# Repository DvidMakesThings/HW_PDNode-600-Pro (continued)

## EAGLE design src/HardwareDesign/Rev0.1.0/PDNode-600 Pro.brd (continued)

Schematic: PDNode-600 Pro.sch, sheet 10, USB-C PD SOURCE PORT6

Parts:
C136, C137: 1uF 10V; 0201
C138: 1uF 50V; C0603
C139: 4.7nF; C0402
C140: 4.7uF; C0402
C141, C142, C143: 10nF; 0201
C144, C145: 100nF; C0402
C146, C147, C148, C149: 10uF 50V; C0805
C150, C151, C152, C153: 22uF 50V; C0805
C154: 100nF; 0201
IC20: STUSB4710AQ1TR; QFN50P300X300X55-16N
IC32: TPS552882; RPM0026A-MFG
IC33: INA219BIDCNT; SOT23-8
L7: 4.7uH 744771004; WE-PD_1280
PORT6: 632722100213
R160: 200K; R0201
R161: 12.7K 0.1%; R0201
R162, R163: 4.64K 0.1%; R0201
R164: 8.87K 0.1%; R0201
R165: 30.9K 0.1%; R0201
R166: 100K; R0201
R167: DNI; R0201
R168, R169, R172: 10K; 0402
R170, R182: 10K; R0201
R171: 2.2K; R0201
R173, R179: 0.010R; 2512
R174: 6.19K; R0201
R175: 49.9K; R0201
R176, R178: 19.9K; R0201
R177: 150K; R0201
R180, R181: 1K; R0201
T31, T32, T33: DMP3013SFV; POWERDI3333-8_UX_DIO-L
T34, T35: BSZ065N06LS5ATMA1; POWERDI3333-8_UX_DIO-L

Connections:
+3V3: C154.1, IC33.4 (VCC), IC33.7 (A0), R166.1, R182.1; also elsewhere on the board
+24V_B: C146.1, C147.1, C148.1, C149.1, IC32.3 (VIN), T35.5 (D), T35.6 (D), T35.7 (D), T35.8 (D), T35.9 (D); also elsewhere on the board
AGND: C139.2, PORT6.S1 (SHIELD1), PORT6.S2 (SHIELD1), PORT6.S3 (SHIELD1), PORT6.S4 (SHIELD1), R172.2; also elsewhere on the board
CC1_PORT6: IC20.2 (CC1), PORT6.A5 (CC1)
CC2_PORT6: IC20.3 (CC2), PORT6.B5 (CC2)
EN_PORT6: IC32.4 (EN), R182.2; also elsewhere on the board
GND: C136.2, C137.2, C138.2, C139.1, C140.2, C141.2, C142.2, C143.2, C146.2, C147.2, C148.2, C149.2, C150.2, C151.2, C152.2, C153.2, C154.2, IC20.6 (GND), IC32.9 (PGND), IC32.10 (AGND), IC32.24 (PGND), IC33.3 (GND), IC33.8 (A1), PORT6.A12 (GND1), PORT6.B12 (GND2), R165.2, R167.2, R168.2, R172.1, R174.2, R175.2, R176.2, R177.2, T34.1 (S), T34.2 (S), T34.3 (S); also elsewhere on the board
IN1_PORT6: IC20.12 (VBUS_SENSE), IC33.1 (IN+), R173.1, T33.5 (D), T33.6 (D), T33.7 (D), T33.8 (D), T33.9 (D)
IN2_PORT6: IC33.2 (IN-), PORT6.A9 (VBUS1), PORT6.B9 (VBUS2), R173.2
unnamed: IC32.14 (FB), R160.2, R161.1
unnamed: IC20.11 (SEL_PDO5), R161.2, R162.1
unnamed: IC20.10 (SEL_PDO4), R162.2, R163.1
unnamed: IC20.7 (SEL_PDO3), R163.2, R164.1
unnamed: IC20.8 (SEL_PDO2), R164.2, R165.1
unnamed: C136.1, IC20.15 (VREG1V2)
unnamed: C137.1, IC20.16 (VREG2V7)
unnamed: IC20.9 (ADDR0), R166.2, R167.1
unnamed: R168.1, T31.5 (D), T31.6 (D), T31.7 (D), T31.8 (D), T31.9 (D)
unnamed: IC20.13 (VBUS_DISCH), R169.2, T31.4 (G)
unnamed: R170.1, T32.1 (S), T32.2 (S), T32.3 (S), T33.1 (S), T33.2 (S), T33.3 (S)
unnamed: R170.2, R171.1, T32.4 (G), T33.4 (G)
unnamed: IC20.14 (VBUS_EN_SRC), R171.2
unnamed: C143.1, R178.2
unnamed: IC32.8 (FSW), R175.1
unnamed: C141.1, IC32.7 (DITH_SYNC)
unnamed: IC32.15 (MODE), R174.1
unnamed: IC32.17 (ILIM), R176.1
unnamed: IC32.16 (CDC), R177.1
unnamed: C142.1, IC32.18 (COMP), R178.1
unnamed: C140.1, IC32.19 (VCC)
unnamed: C144.1, IC32.23 (SW1), L7.1, T34.5 (D), T34.6 (D), T34.7 (D), T34.8 (D), T34.9 (D), T35.1 (S), T35.2 (S), T35.3 (S)
unnamed: C145.1, IC32.21 (SW2), IC32.25 (SW2), L7.2
unnamed: C144.2, IC32.22 (BOOT1)
unnamed: C145.2, IC32.20 (BOOT2)
unnamed: R181.2, T35.4 (G)
unnamed: R180.2, T34.4 (G)
unnamed: IC32.1 (DR1L), R180.1
unnamed: IC32.2 (DR1H), R181.1
TCA2_I2C_SCL: IC20.4 (SCL); also elsewhere on the board
TCA2_I2C_SDA: IC20.5 (SDA); also elsewhere on the board
TCA5_I2C_SCL: IC33.5 (SCL); also elsewhere on the board
TCA5_I2C_SDA: IC33.6 (SDA); also elsewhere on the board
VOUT_PORT6: C150.1, C151.1, C152.1, C153.1, IC32.11 (VOUT), IC32.12 (ISP), IC32.26 (VOUT), R179.1
VSRC6: C138.1, IC20.1 (VDD), IC32.13 (ISN), R160.1, R169.1, R179.2, T31.1 (S), T31.2 (S), T31.3 (S), T32.5 (D), T32.6 (D), T32.7 (D), T32.8 (D), T32.9 (D)

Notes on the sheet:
PDNode-600 Pro
DvidMakesThings
David Sipos @2025
USB-C PD SOURCE PORT6
CURRENT MEASUREMENT
USB-C PD PORT6
v0.1.0
Output voltage: 5 V to 20 V Output current limit: 5 A
PD Ladder - TPS552882 (VREF = 1.20V, Rtop = 200kΩ) R25 = 12.7k → VOUT ≈ 20.10V R26 = 4.64k → VOUT ≈ 15.04V R27 = 4.64k → VOUT ≈ 12.12V R28 = 8.87k → VOUT ≈ 8.98V R29 = 30.9k → VOUT ≈ 5.09V Cumulative Rbottom = 61.75kΩ
Address: 0x40
Address: 0x28

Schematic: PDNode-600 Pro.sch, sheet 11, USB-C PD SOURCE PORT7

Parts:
C155, C156: 1uF 10V; 0201
C157: 1uF 50V; C0603
C158: 4.7nF; C0402
C159: 4.7uF; C0402
C160, C161, C162: 10nF; 0201
C163, C164: 100nF; C0402
C165, C166, C167, C168: 10uF 50V; C0805
C169, C170, C171, C172: 22uF 50V; C0805
C173: 100nF; 0201
IC23: STUSB4710AQ1TR; QFN50P300X300X55-16N
IC35: TPS552882; RPM0026A-MFG
IC36: INA219BIDCNT; SOT23-8
L8: 4.7uH 744771004; WE-PD_1280
PORT7: 632722100213
R183: 200K; R0201
R184: 12.7K 0.1%; R0201
R185, R186: 4.64K 0.1%; R0201
R187: 8.87K 0.1%; R0201
R188: 30.9K 0.1%; R0201
R189: DNI; R0201
R190: 100K; R0201
R191, R192, R195: 10K; 0402
R193, R218: 10K; R0201
R194: 2.2K; R0201
R196, R202: 0.010R; 2512
R197: 6.19K; R0201
R198: 49.9K; R0201
R199, R201: 19.9K; R0201
R200: 150K; R0201
R203, R204: 1K; R0201
T36, T37, T38: DMP3013SFV; POWERDI3333-8_UX_DIO-L
T39, T40: BSZ065N06LS5ATMA1; POWERDI3333-8_UX_DIO-L

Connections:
+3V3: C173.1, IC36.4 (VCC), IC36.8 (A1), R189.1, R218.1; also elsewhere on the board
+24V_B: C165.1, C166.1, C167.1, C168.1, IC35.3 (VIN), T40.5 (D), T40.6 (D), T40.7 (D), T40.8 (D), T40.9 (D); also elsewhere on the board
AGND: C158.2, PORT7.S1 (SHIELD1), PORT7.S2 (SHIELD1), PORT7.S3 (SHIELD1), PORT7.S4 (SHIELD1), R195.2; also elsewhere on the board
CC1_PORT7: IC23.2 (CC1), PORT7.A5 (CC1)
CC2_PORT7: IC23.3 (CC2), PORT7.B5 (CC2)
EN_PORT7: IC35.4 (EN), R218.2; also elsewhere on the board
GND: C155.2, C156.2, C157.2, C158.1, C159.2, C160.2, C161.2, C162.2, C165.2, C166.2, C167.2, C168.2, C169.2, C170.2, C171.2, C172.2, C173.2, IC23.6 (GND), IC35.9 (PGND), IC35.10 (AGND), IC35.24 (PGND), IC36.3 (GND), IC36.7 (A0), PORT7.A12 (GND1), PORT7.B12 (GND2), R188.2, R190.2, R191.2, R195.1, R197.2, R198.2, R199.2, R200.2, T39.1 (S), T39.2 (S), T39.3 (S); also elsewhere on the board
IN1_PORT7: IC23.12 (VBUS_SENSE), IC36.1 (IN+), R196.1, T38.5 (D), T38.6 (D), T38.7 (D), T38.8 (D), T38.9 (D)
IN2_PORT7: IC36.2 (IN-), PORT7.A9 (VBUS1), PORT7.B9 (VBUS2), R196.2
unnamed: IC35.14 (FB), R183.2, R184.1
unnamed: IC23.11 (SEL_PDO5), R184.2, R185.1
unnamed: IC23.10 (SEL_PDO4), R185.2, R186.1
unnamed: IC23.7 (SEL_PDO3), R186.2, R187.1
unnamed: IC23.8 (SEL_PDO2), R187.2, R188.1
unnamed: C155.1, IC23.15 (VREG1V2)
unnamed: C156.1, IC23.16 (VREG2V7)
unnamed: IC23.9 (ADDR0), R189.2, R190.1
unnamed: R191.1, T36.5 (D), T36.6 (D), T36.7 (D), T36.8 (D), T36.9 (D)
unnamed: IC23.13 (VBUS_DISCH), R192.2, T36.4 (G)
unnamed: R193.1, T37.1 (S), T37.2 (S), T37.3 (S), T38.1 (S), T38.2 (S), T38.3 (S)
unnamed: R193.2, R194.1, T37.4 (G), T38.4 (G)
unnamed: IC23.14 (VBUS_EN_SRC), R194.2
unnamed: C162.1, R201.2
unnamed: IC35.8 (FSW), R198.1
unnamed: C160.1, IC35.7 (DITH_SYNC)
unnamed: IC35.15 (MODE), R197.1
unnamed: IC35.17 (ILIM), R199.1
unnamed: IC35.16 (CDC), R200.1
unnamed: C161.1, IC35.18 (COMP), R201.1
unnamed: C159.1, IC35.19 (VCC)
unnamed: C163.1, IC35.23 (SW1), L8.1, T39.5 (D), T39.6 (D), T39.7 (D), T39.8 (D), T39.9 (D), T40.1 (S), T40.2 (S), T40.3 (S)
unnamed: C164.1, IC35.21 (SW2), IC35.25 (SW2), L8.2
unnamed: C163.2, IC35.22 (BOOT1)
unnamed: C164.2, IC35.20 (BOOT2)
unnamed: R204.2, T40.4 (G)
unnamed: R203.2, T39.4 (G)
unnamed: IC35.1 (DR1L), R203.1
unnamed: IC35.2 (DR1H), R204.1
TCA3_I2C_SCL: IC23.4 (SCL); also elsewhere on the board
TCA3_I2C_SDA: IC23.5 (SDA); also elsewhere on the board
TCA5_I2C_SCL: IC36.5 (SCL); also elsewhere on the board
TCA5_I2C_SDA: IC36.6 (SDA); also elsewhere on the board
VOUT_PORT7: C169.1, C170.1, C171.1, C172.1, IC35.11 (VOUT), IC35.12 (ISP), IC35.26 (VOUT), R202.1
VSRC7: C157.1, IC23.1 (VDD), IC35.13 (ISN), R183.1, R192.1, R202.2, T36.1 (S), T36.2 (S), T36.3 (S), T37.5 (D), T37.6 (D), T37.7 (D), T37.8 (D), T37.9 (D)

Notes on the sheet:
PDNode-600 Pro
DvidMakesThings
David Sipos @2025
USB-C PD SOURCE PORT7
CURRENT MEASUREMENT
USB-C PD PORT7
v0.1.0
Output voltage: 5 V to 20 V Output current limit: 5 A
PD Ladder - TPS552882 (VREF = 1.20V, Rtop = 200kΩ) R25 = 12.7k → VOUT ≈ 20.10V R26 = 4.64k → VOUT ≈ 15.04V R27 = 4.64k → VOUT ≈ 12.12V R28 = 8.87k → VOUT ≈ 8.98V R29 = 30.9k → VOUT ≈ 5.09V Cumulative Rbottom = 61.75kΩ
Address: 0x40
Address: 0x28

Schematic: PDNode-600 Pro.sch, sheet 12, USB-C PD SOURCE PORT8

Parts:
C174, C175: 1uF 10V; 0201
C197: 1uF 50V; C0603
C198: 4.7nF; C0402
C199: 4.7uF; C0402
C200, C201, C202: 10nF; 0201
C203, C204: 100nF; C0402
C205, C206, C207, C208: 10uF 50V; C0805
C209, C210, C211, C240: 22uF 50V; C0805
C241: 100nF; 0201
IC30: STUSB4710AQ1TR; QFN50P300X300X55-16N
IC41: TPS552882; RPM0026A-MFG
IC44: INA219BIDCNT; SOT23-8
L9: 4.7uH 744771004; WE-PD_1280
PORT8: 632722100213
R219: 200K; R0201
R220: 12.7K 0.1%; R0201
R221, R222: 4.64K 0.1%; R0201
R223: 8.87K 0.1%; R0201
R224: 30.9K 0.1%; R0201
R245: 100K; R0201
R246: DNI; R0201
R247, R248, R261: 10K; 0402
R259, R275: 10K; R0201
R260: 2.2K; R0201
R262, R272: 0.010R; 2512
R267: 6.19K; R0201
R268: 49.9K; R0201
R269, R271: 19.9K; R0201
R270: 150K; R0201
R273, R274: 1K; R0201
T41, T42, T43: DMP3013SFV; POWERDI3333-8_UX_DIO-L
T44, T45: BSZ065N06LS5ATMA1; POWERDI3333-8_UX_DIO-L

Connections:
+3V3: C241.1, IC44.4 (VCC), IC44.7 (A0), IC44.8 (A1), R245.1, R275.1; also elsewhere on the board
+24V_B: C205.1, C206.1, C207.1, C208.1, IC41.3 (VIN), T45.5 (D), T45.6 (D), T45.7 (D), T45.8 (D), T45.9 (D); also elsewhere on the board
AGND: C198.2, PORT8.S1 (SHIELD1), PORT8.S2 (SHIELD1), PORT8.S3 (SHIELD1), PORT8.S4 (SHIELD1), R261.2; also elsewhere on the board
CC1_PORT8: IC30.2 (CC1), PORT8.A5 (CC1)
CC2_PORT8: IC30.3 (CC2), PORT8.B5 (CC2)
EN_PORT8: IC41.4 (EN), R275.2; also elsewhere on the board
GND: C174.2, C175.2, C197.2, C198.1, C199.2, C200.2, C201.2, C202.2, C205.2, C206.2, C207.2, C208.2, C209.2, C210.2, C211.2, C240.2, C241.2, IC30.6 (GND), IC41.9 (PGND), IC41.10 (AGND), IC41.24 (PGND), IC44.3 (GND), PORT8.A12 (GND1), PORT8.B12 (GND2), R224.2, R246.2, R247.2, R261.1, R267.2, R268.2, R269.2, R270.2, T44.1 (S), T44.2 (S), T44.3 (S); also elsewhere on the board
IN1_PORT8: IC30.12 (VBUS_SENSE), IC44.1 (IN+), R262.1, T43.5 (D), T43.6 (D), T43.7 (D), T43.8 (D), T43.9 (D)
IN2_PORT8: IC44.2 (IN-), PORT8.A9 (VBUS1), PORT8.B9 (VBUS2), R262.2
unnamed: IC41.14 (FB), R219.2, R220.1
unnamed: IC30.11 (SEL_PDO5), R220.2, R221.1
unnamed: IC30.10 (SEL_PDO4), R221.2, R222.1
unnamed: IC30.7 (SEL_PDO3), R222.2, R223.1
unnamed: IC30.8 (SEL_PDO2), R223.2, R224.1
unnamed: C174.1, IC30.15 (VREG1V2)
unnamed: C175.1, IC30.16 (VREG2V7)
unnamed: IC30.9 (ADDR0), R245.2, R246.1
unnamed: R247.1, T41.5 (D), T41.6 (D), T41.7 (D), T41.8 (D), T41.9 (D)
unnamed: IC30.13 (VBUS_DISCH), R248.2, T41.4 (G)
unnamed: R259.1, T42.1 (S), T42.2 (S), T42.3 (S), T43.1 (S), T43.2 (S), T43.3 (S)
unnamed: R259.2, R260.1, T42.4 (G), T43.4 (G)
unnamed: IC30.14 (VBUS_EN_SRC), R260.2
unnamed: C202.1, R271.2
unnamed: IC41.8 (FSW), R268.1
unnamed: C200.1, IC41.7 (DITH_SYNC)
unnamed: IC41.15 (MODE), R267.1
unnamed: IC41.17 (ILIM), R269.1
unnamed: IC41.16 (CDC), R270.1
unnamed: C201.1, IC41.18 (COMP), R271.1
unnamed: C199.1, IC41.19 (VCC)
unnamed: C203.1, IC41.23 (SW1), L9.1, T44.5 (D), T44.6 (D), T44.7 (D), T44.8 (D), T44.9 (D), T45.1 (S), T45.2 (S), T45.3 (S)
unnamed: C204.1, IC41.21 (SW2), IC41.25 (SW2), L9.2
unnamed: C203.2, IC41.22 (BOOT1)
unnamed: C204.2, IC41.20 (BOOT2)
unnamed: R274.2, T45.4 (G)
unnamed: R273.2, T44.4 (G)
unnamed: IC41.1 (DR1L), R273.1
unnamed: IC41.2 (DR1H), R274.1
TCA3_I2C_SCL: IC30.4 (SCL); also elsewhere on the board
TCA3_I2C_SDA: IC30.5 (SDA); also elsewhere on the board
TCA5_I2C_SCL: IC44.5 (SCL); also elsewhere on the board
TCA5_I2C_SDA: IC44.6 (SDA); also elsewhere on the board
VOUT_PORT8: C209.1, C210.1, C211.1, C240.1, IC41.11 (VOUT), IC41.12 (ISP), IC41.26 (VOUT), R272.1
VSRC8: C197.1, IC30.1 (VDD), IC41.13 (ISN), R219.1, R248.1, R272.2, T41.1 (S), T41.2 (S), T41.3 (S), T42.5 (D), T42.6 (D), T42.7 (D), T42.8 (D), T42.9 (D)

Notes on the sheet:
PDNode-600 Pro
DvidMakesThings
David Sipos @2025
USB-C PD SOURCE PORT8
CURRENT MEASUREMENT
USB-C PD PORT8
v0.1.0
Output voltage: 5 V to 20 V Output current limit: 5 A
PD Ladder - TPS552882 (VREF = 1.20V, Rtop = 200kΩ) R25 = 12.7k → VOUT ≈ 20.10V R26 = 4.64k → VOUT ≈ 15.04V R27 = 4.64k → VOUT ≈ 12.12V R28 = 8.87k → VOUT ≈ 8.98V R29 = 30.9k → VOUT ≈ 5.09V Cumulative Rbottom = 61.75kΩ
Address: 0x40
Address: 0x28

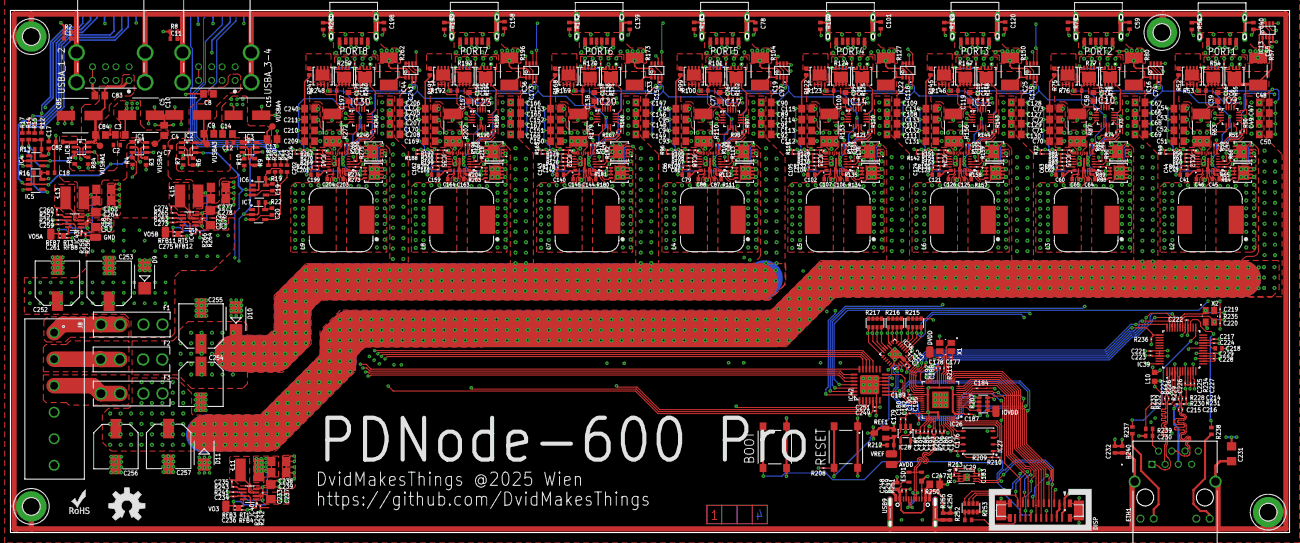
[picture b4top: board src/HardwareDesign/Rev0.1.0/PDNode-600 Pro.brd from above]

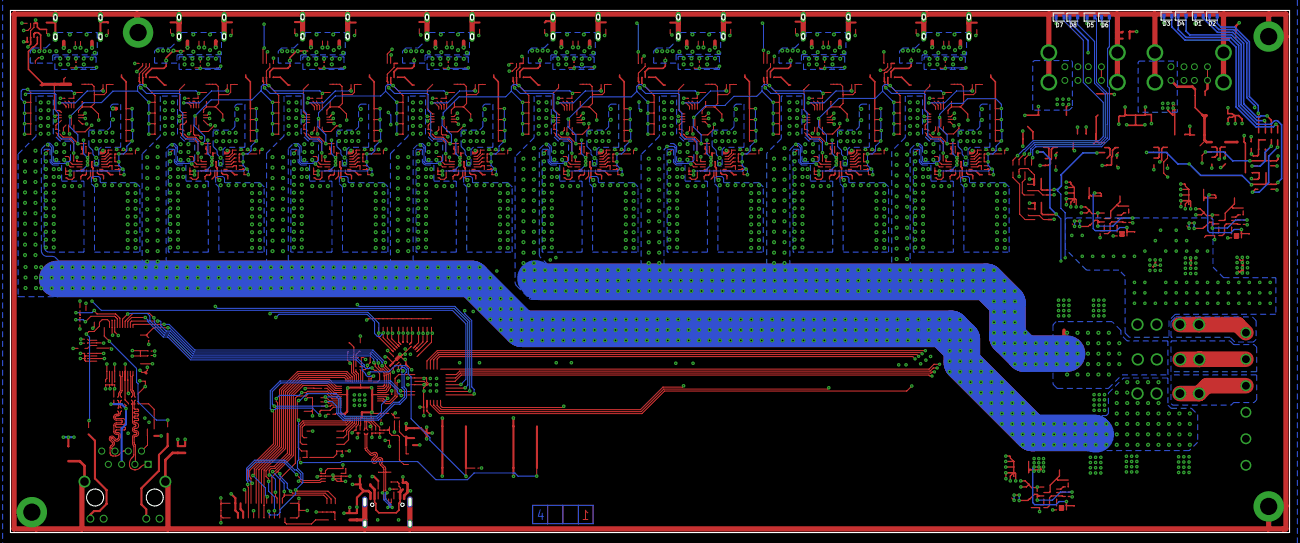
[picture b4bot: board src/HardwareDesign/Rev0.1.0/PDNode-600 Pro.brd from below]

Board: 4 copper layers, 245.0 x 100.0 mm, 654 parts (8 on the bottom side), 432 nets.

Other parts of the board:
U$1: ROHS_LOGO_0.18_IN
U$2: OSHW-LOGO-L

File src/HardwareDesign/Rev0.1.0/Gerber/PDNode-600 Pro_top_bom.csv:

Comment,Designator,Footprint,LCSC Part #
,USB9,USB-C,
0.010R,R57 R63 R80 R87 R104 R110 R127 R133 R150 R156 R173 R179 R196 R202 R262 R272,2512,C105142
1K,R12 R14 R15 R17 R18 R20 R21 R23,0402,C11702
1K,R64 R65 R88 R89 R111 R112 R134 R135 R157 R158 R180 R181 R203 R204 R210 R211 R273 R274,R0201,C100125
1M,R235,R0201,C102686
1M,R255,0402,C26083
1uF,C179,C0402,C52923
1uF,C213 C251,0201,C87143
1uF 10V,C6 C16 C56 C57 C75 C76 C98 C99 C117 C118 C136 C137 C155 C156 C174 C175,0201,C76935
1uF 50V,C39 C58 C77 C100 C119 C138 C157 C197,C0603,C15849
2.2K,R55 R78 R102 R125 R148 R171 R194 R260,R0201,C142018
2.2K 1%,R249,R0201,C142018
3.3R,R226 R227 R228 R229,R0201,C158547
4.2uH,L11,SRR5228A,
4.7K,R212,0402,C25900
4.7K,R214 R236,R0201,C138135
4.7nF,C1 C11 C40 C59 C78 C101 C120 C139 C158 C198 C232 C250,C0402,C1538
4.7uF,C41 C60 C79 C102 C121 C140 C159 C199 C218,C0402,C23733
4.7uH 744771004,L2 L3 L4 L5 L6 L7 L8 L9,WE-PD_1280,
4.9uH,L13 L15,SRR5228A,
4.64K 0.1%,R46 R47 R69 R70 R93 R94 R116 R117 R139 R140 R162 R163 R185 R186 R221 R222,R0201,C270725
4D03WGJ0332T5E,R207,742C083103JP,C12013
4D03WGJ0332T5E,R215 R216 R217,YC164-JR-0733RL,C12013
4D03WGJ0332T5E,R253,742C083103JP,C12013
5.1K,R250 R251,R0201,C100142
6.8nF,C215 C216,0201,C285015
6.19K,R58 R81 R105 R128 R151 R174 R197 R267,R0201,C158394
7.5K,R242 R256 R264,R0201,C158362
7.5K 1%,RFB8 RFB12,R0201,C158362
8.87K 0.1%,R48 R71 R95 R118 R141 R164 R187 R223,R0201,C332577
10K,R1 R2 R4 R7 R8 R10 R13 R16 R19 R22 R52 R53,0402,C25744
10K,R54,R0201,C100126
10K,R56,0402,C25744
10K,R66,R0201,C100126
10K,R75 R76,0402,C25744
10K,R77,R0201,C100126
10K,R79,0402,C25744
10K,R90,R0201,C100126
10K,R99 R100,0402,C25744
10K,R101,R0201,C100126
10K,R103,0402,C25744
10K,R113,R0201,C100126
10K,R122 R123,0402,C25744
10K,R124,R0201,C100126
10K,R126,0402,C25744
10K,R136,R0201,C100126
10K,R145 R146,0402,C25744
10K,R147,R0201,C100126
10K,R149,0402,C25744
10K,R159,R0201,C100126
10K,R168 R169,0402,C25744
10K,R170,R0201,C100126
10K,R172,0402,C25744
10K,R182,R0201,C100126
10K,R191 R192,0402,C25744
10K,R193,R0201,C100126
10K,R195,0402,C25744
10K,R208 R218,R0201,C100126
10K,R240 R247 R248 R252,0402,C25744
10K,R259,R0201,C100126
10K,R261,0402,C25744
10K,R275,R0201,C100126
10R,R243 R257 R265,R0201,C100126
10nF,C42 C43 C44 C61 C62 C63 C80 C81 C86 C103 C104 C105 C122 C123 C124 C141 C142 C143 C160 C161 C162 C200 C201 C202,0201,C285010
10uF,C3 C4 C8 C9 C13 C14 C83 C84,C0805,C15850
10uF,C247,0805,C15850
10uF 50V,C47 C48 C49 C50 C66 C67 C68 C69 C89 C90 C91 C92 C108 C109 C110 C111 C127 C128 C129 C130 C146 C147 C148 C149 C165 C166 C167 C168 C205 C206 C207 C208,C0805,C440198
12.4K 1%,R234,R0201,C423760
12.7K 0.1%,R11 R68 R92 R115 R138 R161 R184 R220,R0201,C423755
12.7K 1%,RFB4,R0201,C166367
12MHz,X1,WE-XTAL_CFPX-180,C9002
15pF,C177 C178,0201,C64554
18pF,C219 C220,0201,C85892
19.9K,R60 R62 R83 R86 R107 R109 R130 R132 R153 R155 R176 R178 R199 R201 R269 R271,R0201,C226463
20K 1%,R3 R6 R9 R84,0402,C25765
20K 1%,RT3 RT5,R0201,C226463
22nF,C230,C0402,C1532
22uF - 10V,C238 C239 C263 C264 C277 C278,C1206,C12891
22uF 25V,C237 C262 C276,C1206,C12891
22uF 50V,C51 C52 C53 C54 C70 C71 C72 C73 C93 C94 C95 C96 C112 C113 C114 C115 C131 C132 C133 C134 C150 C151 C152 C153 C169 C170 C171 C172 C209 C210 C211 C240,C0805,C45783
25MHz,X2,3.2X2.5_KX-7,
27R,R205 R206,R0201,C273268
30.9K 0.1%,R49 R72 R96 R119 R142 R165 R188 R224,R0201,C158612
33K,RT1,R0201,C100136
33pF,C236 C261 C275,0201,C277477
40.2K,RFB3 RFB7 RFB11,R0201,C166207
49.9K,R59 R82 R106 R129 R152 R175 R198 R268,R0201,C138136
49.9R,R230 R231 R232 R233,R0201,C100141
100K,R51 R73 R98 R120 R144 R166 R190 R244 R245 R258 R266,R0201,C100127
100nF,C2 C7 C12 C17 C18 C19 C20 C45 C46,C0402,C1581
100nF,C55,0201,C49062
100nF,C64 C65,C0402,C1581
100nF,C74,0201,C49062
100nF,C82 C87 C88,C0402,C1581
100nF,C97,0201,C49062
100nF,C106 C107,C0402,C1581
100nF,C116,0201,C49062
100nF,C125 C126,C0402,C1581
100nF,C135,0201,C49062
100nF,C144 C145,C0402,C1581
100nF,C154,0201,C49062
100nF,C163 C164,C0402,C1581
100nF,C173 C176 C180 C181 C182 C183 C184 C185 C186 C187 C188 C189 C190 C191 C192 C193 C194 C195,0201,C49062
100nF,C203 C204,C0402,C1581
100nF,C212 C214 C217 C221 C222 C223 C224 C225 C226 C227 C228 C229 C233 C234 C235 C241,0201,C49062
100nF,C248,0402,C1581
100nF,C249 C258 C259 C260 C272 C273 C274,0201,C49062
100uF 16V,C5 C10 C15 C85,100UF-16V,C37308
150K,R61 R85 R108 R131 R154 R177 R200 R270,R0201,C158794
200K,R5 R67 R91 R114 R137 R160 R183 R219,R0201,C138163
220uF 35V,C252 C253 C254 C255 C256 C257,CAPAE830X1050N,C970697
470R,R237 R238 R239,0402,C25117
499K,R241 R254 R263,R0201,C138138
4.30182E+11,BOOT RESET,4.30182E+11,
6.32722E+11,PORT1 PORT2 PORT3 PORT4 PORT5 PORT6 PORT7 PORT8,6.32722E+11,C283540
AFC11-S20ICC-00,DISP,FPC20,C11073
AP22653W6-7,IC1 IC2 IC3 IC8,SOT23-6,C2158037
BLM18EG221TN1D,L10,0603,C113025
C1206C102KGRACTM,C231,C1206,
CAT24C512HU5IGT3,IC29,SON50P300X200X50-9T130X140N,C153773
DMP3013SFV,T6 T7 T8 T11 T12 T13 T16 T17 T18 T21 T22 T23 T26 T27 T28 T31 T32 T33 T36 T37 T38 T41 T42 T43,POWERDI3333-8_UX_DIO-L,C264098
DNI,R50 R74 R97 R121 R143 R167 R189 R209 R246,R0201,
INA219BIDCNT,IC13 IC16 IC19 IC22 IC25 IC33 IC36 IC44,SOT23-8,C2653868
IPZ40N04S5L-7R4,T9 T14 T19 T24 T29 T34 T39 T44,POWERDI3333-8_UX_DIO-L,
IPZ40N04S5L2R8,T10 T15 T20 T25 T30 T35 T40 T45,POWERDI3333-8_UX_DIO-L,
LM4040BXX,REF1,SOT23,C9409
MCP6001R,IC28,SOT23-5,C154973
MCP23017-E/ML,IC42,QFN28[6X6]ML,C639770
MP2315S,IC40 IC43 IC45,SOT65P280X110-8N,C3031493
NC,R213,R0201,
RP2040,IC26,QFN40P700X700X100-57T510,C2040
SMBJ33A,D9 D10 D11,SMB,C19077586
SN74LVC1G04DBVR,IC4 IC5 IC6 IC7,SOT95P280X145-5N,C7827
SP0503BAHTG-ES,ESD1,SOT143,C19170916
STUSB4710AQ1TR,IC9 IC10 IC11 IC14 IC17 IC20 IC23 IC30,QFN50P300X300X55-16N,
TCA9548ARGER,IC38,QFN50P400X400X100-25T210N,C555456
TP,AVDD DVDD GND IOVDD VO3 VO5A VO5B VREF,TP,
TPB1 27,VUSBA1,B1 27,
TPB1 27,VUSBA2,B1 27,
TPB1 27,VUSBA3,B1 27,
TPB1 27,VUSBA4,B1 27,
TPS552882,IC12 IC15 IC18 IC21 IC24 IC32 IC35 IC41,RPM0026A-MFG,C2876594
W25Q128JVPIQ,IC27,SON127P600X500X75-8N,C190862
W5500,IC39,LQFP48,C32843

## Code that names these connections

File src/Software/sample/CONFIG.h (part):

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/** @name GPIO Assignments
 * @ingroup config01
 * @{ */
#define UART0_RX 0
#define UART0_TX 1
#define I2C1_SDA 2
#define I2C1_SCL 3
#define I2C0_SDA 4
#define I2C0_SCL 5
#define GPIO6 6   // Not used anymore
#define GPIO7 7   // Not used anymore
#define GPIO8 8   // Not used anymore
#define GPIO9 9   // Not used anymore
#define GPIO10 10 // Not used anymore
#define GPIO11 11 // Not used anymore
#define KEY_0 12
#define KEY_1 13
#define KEY_2 14
#define KEY_3 15
#define BUT_PLUS KEY_1
#define BUT_MINUS KEY_0
#define BUT_SET KEY_2
#define BUT_PWR KEY_3
#define W5500_MISO 16
#define W5500_CS 17
#define W5500_SCK 18
#define W5500_MOSI 19
#define W5500_RESET 20
#define W5500_INT 21
#define FAN_CTRL 22 // Fan control (not used)
#define MCP_MB_RST 23
#define MCP_DP_RST 24
#define VREG_EN 25
#define ADC_VUSB 26
#define NC 27 // ADC Temp sensor (not used)
#define PROC_LED 28
#define ADC_12V_MEA 29
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
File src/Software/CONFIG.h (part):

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/* -------------------------------------------------------------------------- */
/*  I2C0 - Onboard EEPROM (AT24C256) + M.2 connector                         */
/* -------------------------------------------------------------------------- */
#define PIN_I2C0_SDA 32 /* I2C0 data  (4.7K pull-up)         */
#define PIN_I2C0_SCL 33 /* I2C0 clock (4.7K pull-up)         */

/* -------------------------------------------------------------------------- */
/*  W5500 Ethernet Control                                                    */
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/* -------------------------------------------------------------------------- */
/*  ADC - Onboard                                                             */
/* -------------------------------------------------------------------------- */
#define PIN_ADC_VUSB 46 /* GPIO46/ADC6 - USB VBUS sense (5.1K-5.1K divider) */
#define PIN_ADC_VREF 47 /* GPIO47/ADC7 - 3.00V 0.1% ref (10K-10K divider)   */

/* -------------------------------------------------------------------------- */
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/* -------------------------------------------------------------------------- */
#define PD_IRQ_EVENT_A2 0 /* MCP23017T INT-A USB-A Signal */
#define PD_IRQ_EVENT_B2 1 /* MCP23017T INT-B USB-A Signal */
#define PIN_I2C1_SDA 2    /* M.2 pin 53 - I2C1 data  (MCP23017) */
#define PIN_I2C1_SCL 3    /* M.2 pin 51 - I2C1 clock (MCP23017) */
#define SPI_MISO 4        /* SPI0 MISO */
#define SPI_CS 5          /* SPI0 CS */
#define SPI_CLK 6         /* SPI0 CLK */
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#define SPI_CS_PORT0 15   /* PDCard SPI0 CS0 */
#define PIN_5V_BUCK_EN 16 /* TPS51225CRUKR 5V Buck Enable */
#define PGOOD_SYSPMIC 17  /* TPS51225CRUKR Power Good */
// #define PIN_GPIO18            18      /* M.2 pin 17 - Unused */
#define PAC_ALERT_P23 19    /* PAC1720 Alert Channel 2-3 */
#define PAC_ALERT_P01 20    /* PAC1720 Alert Channel 0-1 */
#define PIN_MUX_S3 21       /* MUX Select 3 */
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#define PD_IRQ_EVENT_A 26   /* MCP23017T INT-A MCPAddr: 0x23 */
#define PD_IRQ_EVENT_B 27   /* MCP23017T INT-B MCPAddr: 0x23 */

/* GPIO37, GPIO38, GPIO39 are NOT connected on BladeCore-M54E */
#ifdef PIN_GPIO37
#error "GPIO37 is not connected on BladeCore-M54E"
#endif
#ifdef PIN_GPIO38
#error "GPIO38 is not connected on BladeCore-M54E"
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/* -------------------------------------------------------------------------- */
/*  Heartbeat LED - PWM configuration                                         */
/* -------------------------------------------------------------------------- */
/*  GPIO36 -> PWM slice 2, channel A (RP2354B: slice = (gpio >> 1) & 0xF)    */
#define HEARTBEAT_PWM_FREQ_HZ 1000
#define HEARTBEAT_FADE_STEP_MS 8

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/* ========================================================================= */
#define W5500_SPI_INSTANCE ETH_SPI_INSTANCE
#define SPI_SPEED_W5500 ETH_SPI_BAUDRATE
#define W5500_MOSI PIN_ETH_MOSI
#define W5500_MISO PIN_ETH_MISO
#define W5500_SCK PIN_ETH_SCK
#define W5500_CS PIN_ETH_CS
#define W5500_RESET PIN_ETH_RST
#define W5500_INT PIN_ETH_INT

/* ethernet_driver.c gets the rest of its defines from ethernet_config.h */

/* ========================================================================= */
/*  I2C Bus Compatibility Defines                                             */
/* ========================================================================= */
#define I2C0_SDA PIN_I2C0_SDA
#define I2C0_SCL PIN_I2C0_SCL
#define I2C0_SPEED EEPROM_I2C_BAUDRATE
#define I2C1_SDA PIN_I2C1_SDA
#define I2C1_SCL PIN_I2C1_SCL
#define I2C1_SPEED MCP23017_I2C_BAUDRATE

/* ========================================================================= */
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
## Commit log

2025-05-02 Start hardware design
2025-05-05 Hardware design update
2025-05-06 Update hardware design files
2025-05-07 Add BOM
2025-05-22 Update RESET and BOOT part values in hardware design files
2025-09-08 Update licensing to protect hardware components
2026-02-04 Project ramp-up: KiCad transition. Board redesign
2026-02-05 update component lib
2026-02-05 Baseboard design start
2026-02-09 Add bladecore to design
2026-02-13 add datasheets
2026-02-17 almost finished baseboard
2026-02-17 M54 rework
2026-02-24 baseboard development
2026-02-26 add PDCard-4242 with lower profile
2026-02-27 hardware design is close to final status
2026-02-27 add folder structure
2026-02-27 add playground
2026-02-27 fix background transient issue
2026-03-01 update readme, add documentation
2026-03-06 finalized 1.0.0 revision, PCB, PCBA ordered
2026-03-30 minor fixes, start with software
2026-03-30 add provisioning
2026-03-30 fix current reading bug
